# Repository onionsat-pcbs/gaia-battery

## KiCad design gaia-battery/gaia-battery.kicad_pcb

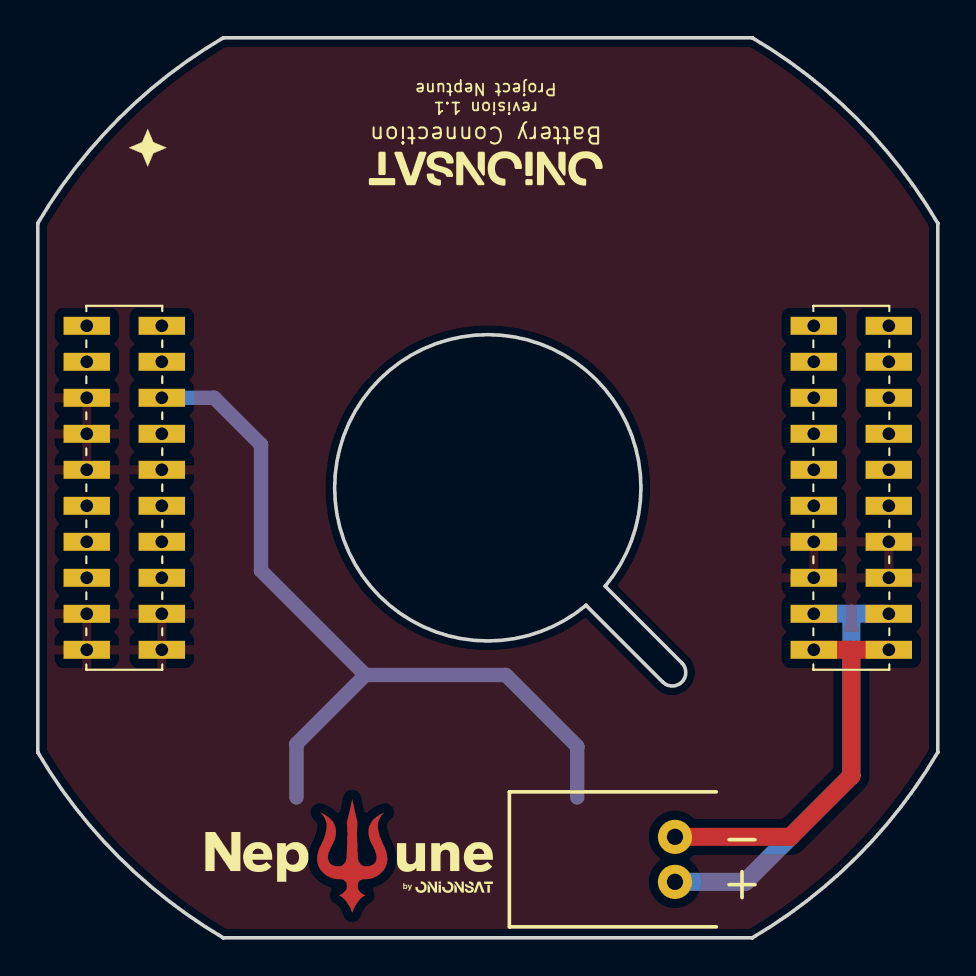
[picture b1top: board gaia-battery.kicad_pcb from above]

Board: 6 copper layers, 50.0 x 50.0 mm, 4 parts (1 on the bottom side), 4 nets.

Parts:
BTc1: Battery_Cell; BAT-SMD_MY-1220-03
J1, J2: Conn_02x10_Odd_Even; Gaia_connector_2_4layer
J3: Conn_01x02_Pin; JT-A2501WR-2P

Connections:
+BATT: J2.17, J2.18, J3.1
-BATT: J2.19, J2.20, J3.2
GND: BTc1.2 (-), J1.5, J1.7, J1.9, J1.10, J1.17, J1.18, J1.19, J1.20, J2.13, J2.14, J2.15, J2.16
unnamed: BTc1.1 (+), J1.6

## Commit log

2025-11-09 ready
2025-11-10 fixing routing problems
2025-12-17 update pushing
2025-12-28 v1.1 - adding rtc battery
2025-12-28 v1.1 gnd fix
